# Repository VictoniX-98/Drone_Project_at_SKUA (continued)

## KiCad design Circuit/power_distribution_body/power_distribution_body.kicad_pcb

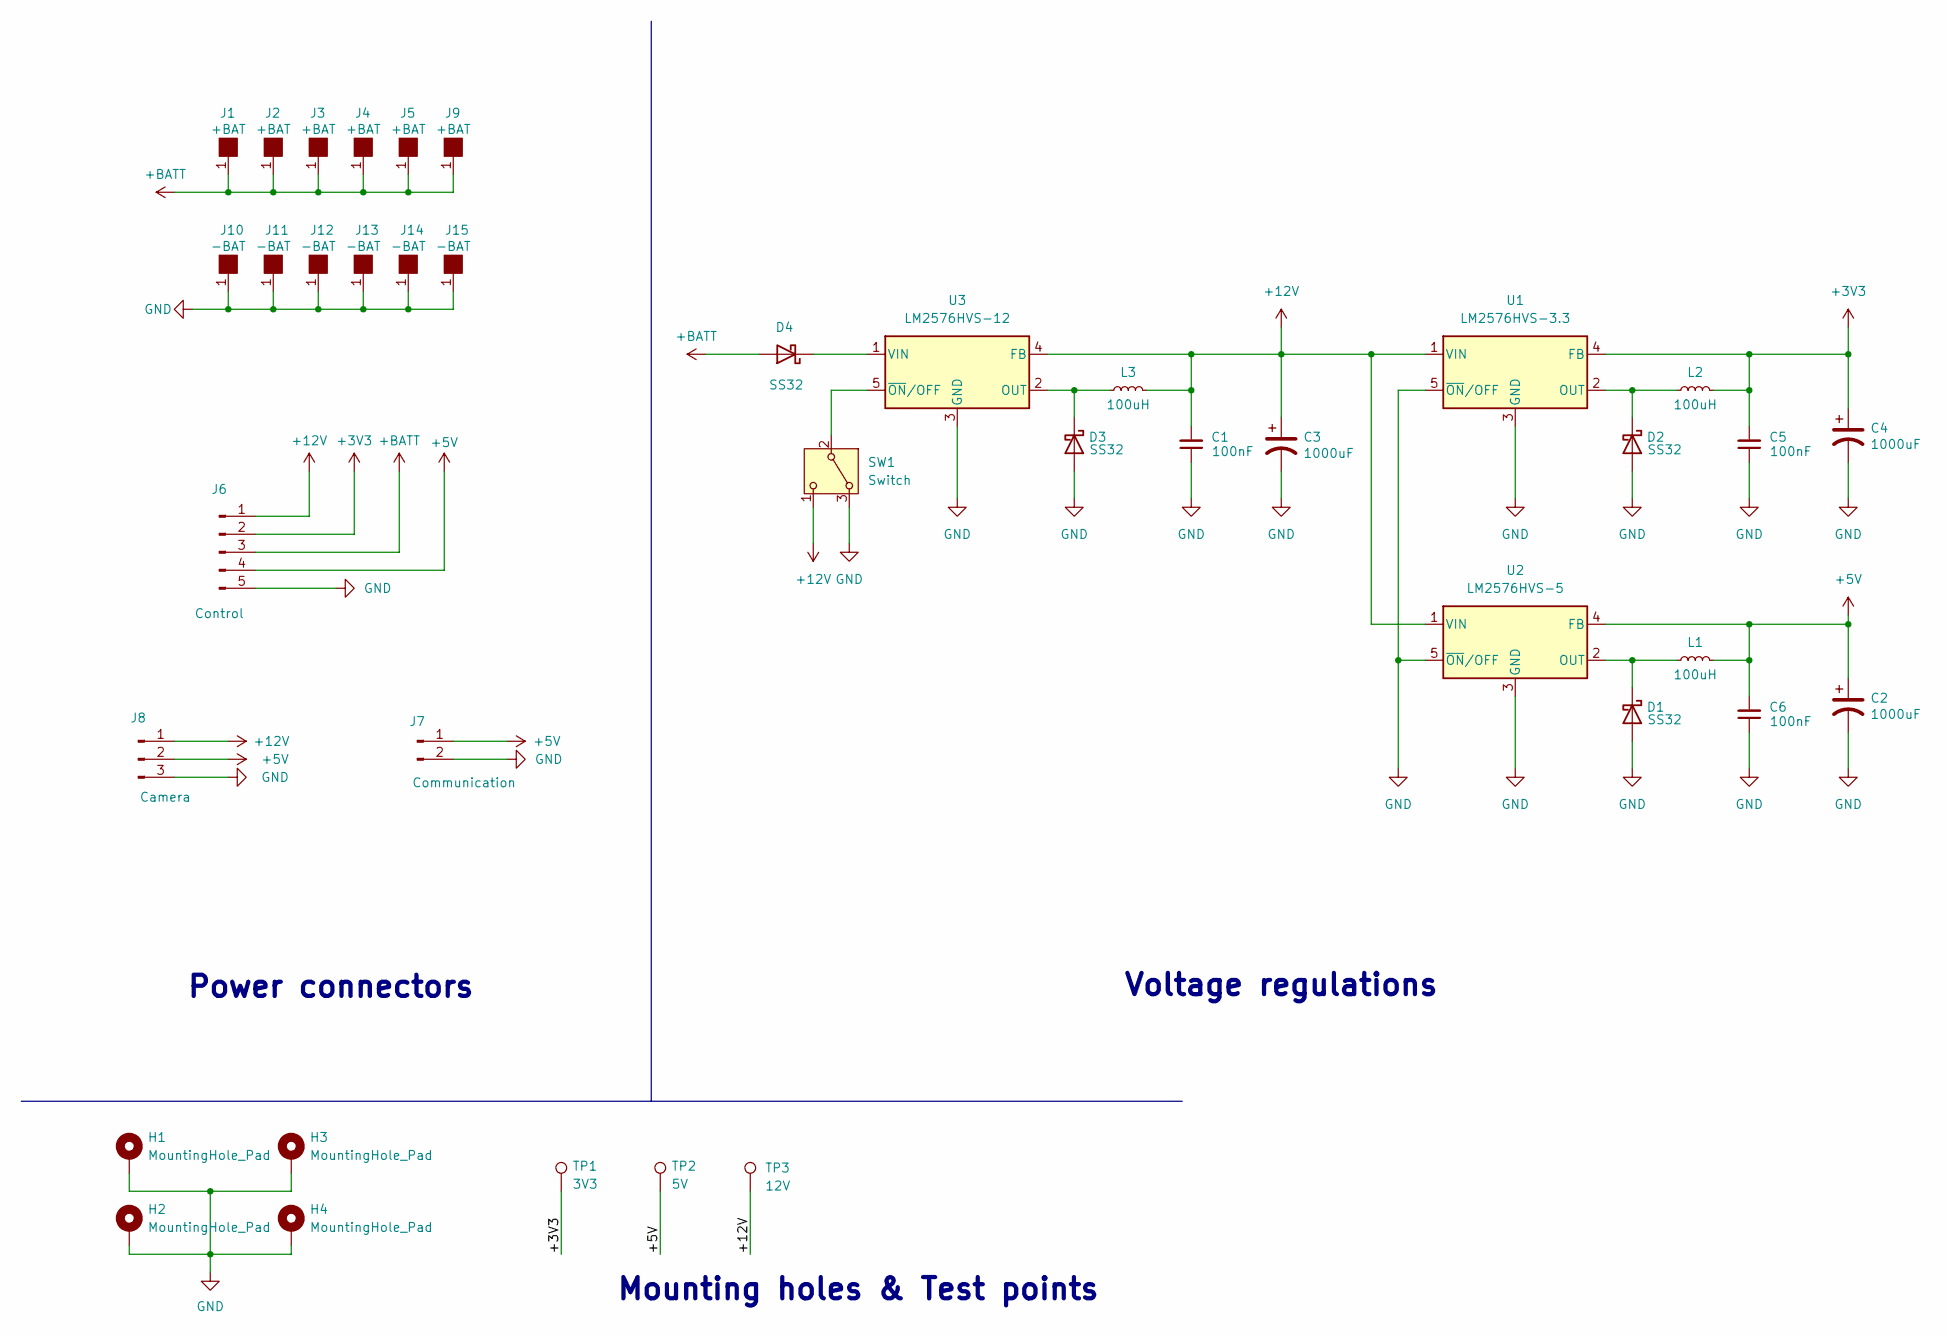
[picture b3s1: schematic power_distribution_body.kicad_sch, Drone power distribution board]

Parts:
C1, C5, C6: 100nF; C_0805_2012Metric_Pad1.18x1.45mm_HandSolder
C2, C3, C4: 1000uF; CP_Radial_D13.0mm_P5.00mm
D1, D2, D3, D4: SS32; D_SMA
H1, H2, H3, H4: MountingHole_Pad; MountingHole_3.5mm_Pad_Via
J1, J2, J3, J4, J5, J9: +BAT; Rectangular_Pad_20x20mm
J6: Control; JST_PH_B5B-PH-K_1x05_P2.00mm_Vertical
J7: Communication; JST_PH_B2B-PH-K_1x02_P2.00mm_Vertical
J8: Camera; JST_PH_B3B-PH-K_1x03_P2.00mm_Vertical
J10, J11, J12, J13, J14, J15: -BAT; Rectangular_Pad_20x20mm
L1, L2, L3: 100uH; L_Radial_D10.0mm_P5.00mm_Fastron_07P
SW1: Switch; SW_Slide_SPDT_Straight_CK_OS102011MS2Q
TP1: 3V3; TestPoint_Pad_D1.0mm
TP2: 5V; TestPoint_Pad_D1.0mm
TP3: 12V; TestPoint_Pad_D1.0mm
U1: LM2576HVS-3.3; TO-263-5_TabPin3
U2: LM2576HVS-5; TO-263-5_TabPin3
U3: LM2576HVS-12; TO-263-5_TabPin3

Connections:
+3V3: C4.1, C5.2, J6.2, L2.2, TP1.1, U1.4 (FB)
+5V: C2.1, C6.2, J6.4, J7.1, J8.2, L1.2, TP2.1, U2.4 (FB)
+12V: C1.2, C3.1, J6.1, J8.1, L3.2, SW1.1 (C), TP3.1, U1.1 (VIN), U2.1 (VIN), U3.4 (FB)
+BATT: D4.2 (A), J1.1, J2.1, J3.1, J4.1, J5.1, J6.3, J9.1
GND: C1.1, C2.2, C3.2, C4.2, C5.1, C6.1, D1.2 (A), D2.2 (A), D3.2 (A), H1.1, H2.1, H3.1, H4.1, J6.5, J7.2, J8.3, J10.1, J11.1, J12.1, J13.1, J14.1, J15.1, SW1.3 (A), U1.3 (GND), U1.5 (~ON/OFF), U2.3 (GND), U2.5 (~ON/OFF), U3.3 (GND)
unnamed: D1.1 (K), L1.1, U2.2 (OUT)
unnamed: D2.1 (K), L2.1, U1.2 (OUT)
unnamed: D3.1 (K), L3.1, U3.2 (OUT)
unnamed: D4.1 (K), U3.1 (VIN)
unnamed: SW1.2 (B), U3.5 (~ON/OFF)

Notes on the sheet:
Voltage regulations
Mounting holes & Test points
Power connectors

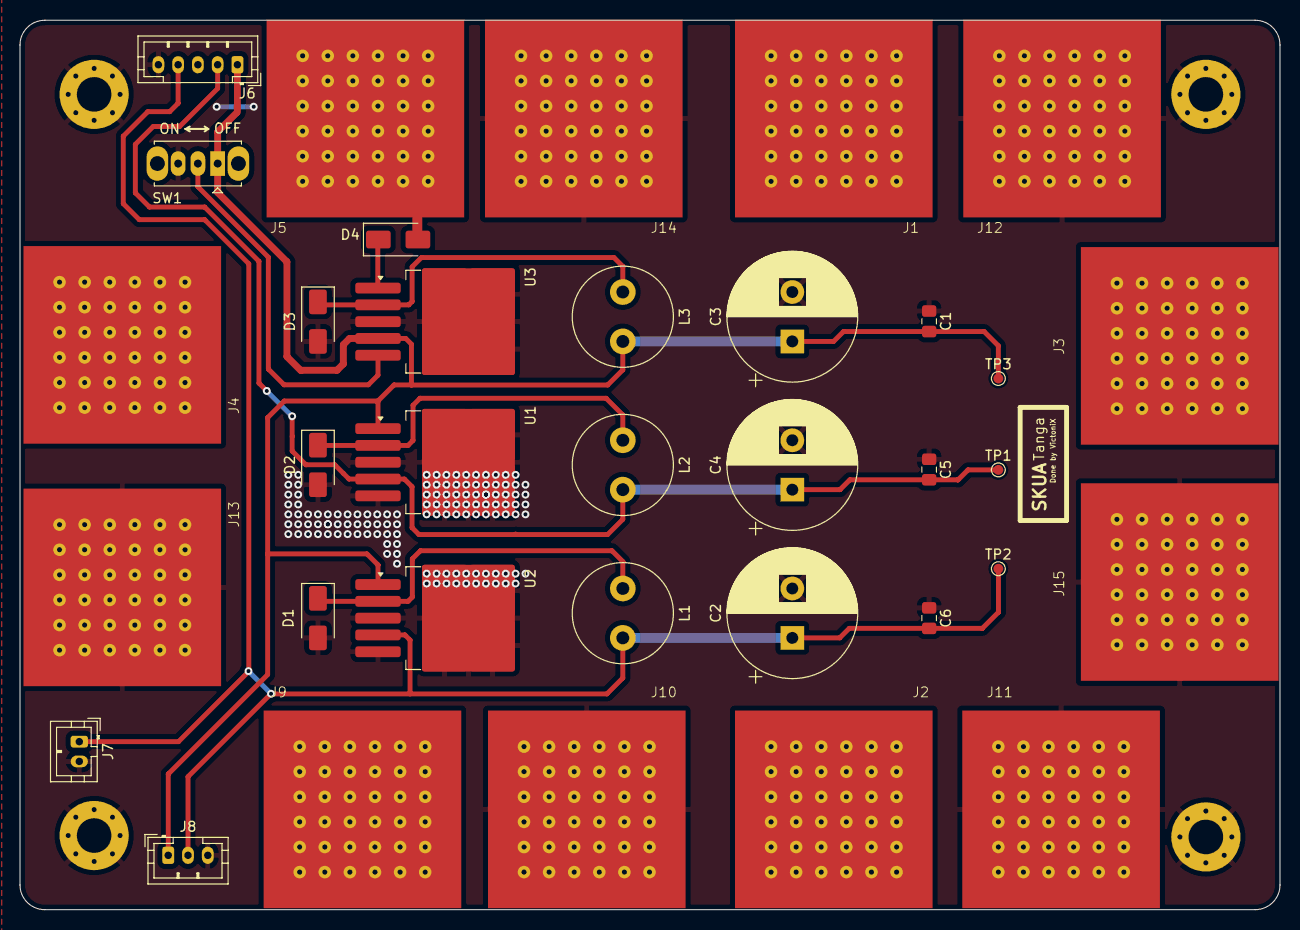
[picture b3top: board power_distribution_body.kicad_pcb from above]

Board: 2 copper layers, 127.5 x 90.0 mm, 39 parts (0 on the bottom side), 10 nets.

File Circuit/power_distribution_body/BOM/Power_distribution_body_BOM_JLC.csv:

Designator,Footprint,Comment
"C1,C5,C6",Capacitor_SMD:C_0805_2012Metric_Pad1.18x1.45mm_HandSolder,100nF
"C2,C3,C4",Capacitor_THT:CP_Radial_D13.0mm_P5.00mm,1000uF
"D1,D2,D3,D4",Diode_SMD:D_SMA,SS32
J6,Connector_JST:JST_PH_B5B-PH-K_1x05_P2.00mm_Vertical,Control
J7,Connector_JST:JST_PH_B2B-PH-K_1x02_P2.00mm_Vertical,Communication
J8,Connector_JST:JST_PH_B3B-PH-K_1x03_P2.00mm_Vertical,Camera
"L1,L2,L3",Inductor_THT:L_Radial_D10.0mm_P5.00mm_Fastron_07P,100uH
SW1,Button_Switch_THT:SW_Slide_SPDT_Straight_CK_OS102011MS2Q,Switch
U1,Package_TO_SOT_SMD:TO-263-5_TabPin3,LM2576HVS-3.3
U2,Package_TO_SOT_SMD:TO-263-5_TabPin3,LM2576HVS-5
U3,Package_TO_SOT_SMD:TO-263-5_TabPin3,LM2576HVS-12

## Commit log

2024-09-01 Add Ground control circuit, Modify the rest and add payment confirmation details from manufacture
